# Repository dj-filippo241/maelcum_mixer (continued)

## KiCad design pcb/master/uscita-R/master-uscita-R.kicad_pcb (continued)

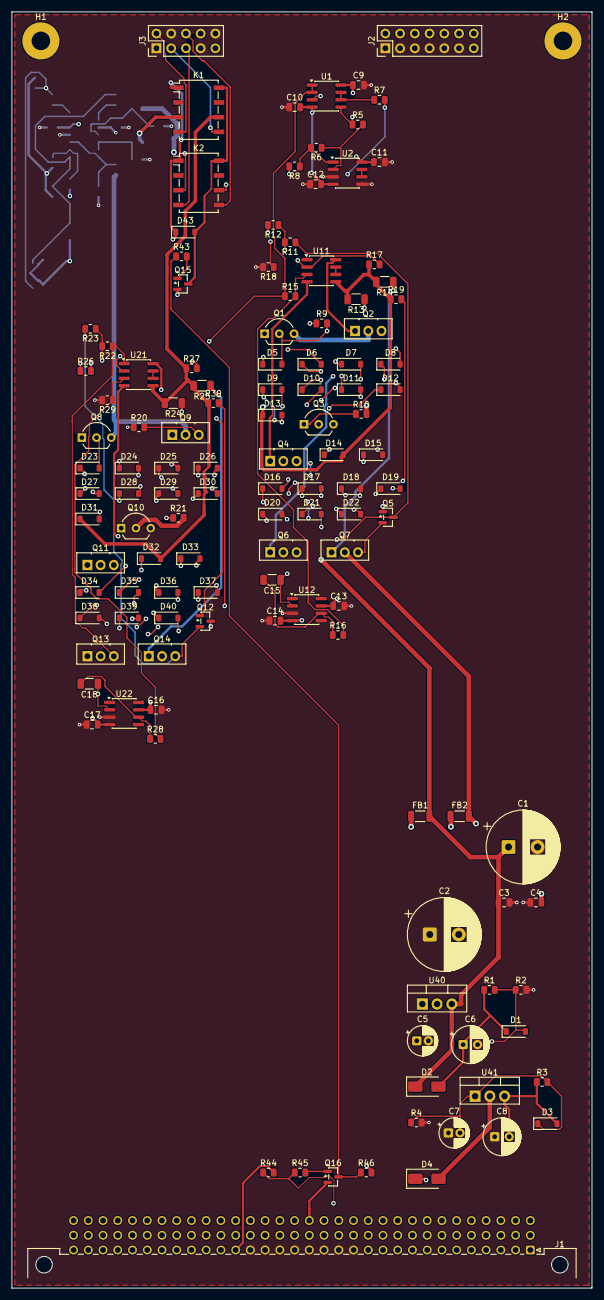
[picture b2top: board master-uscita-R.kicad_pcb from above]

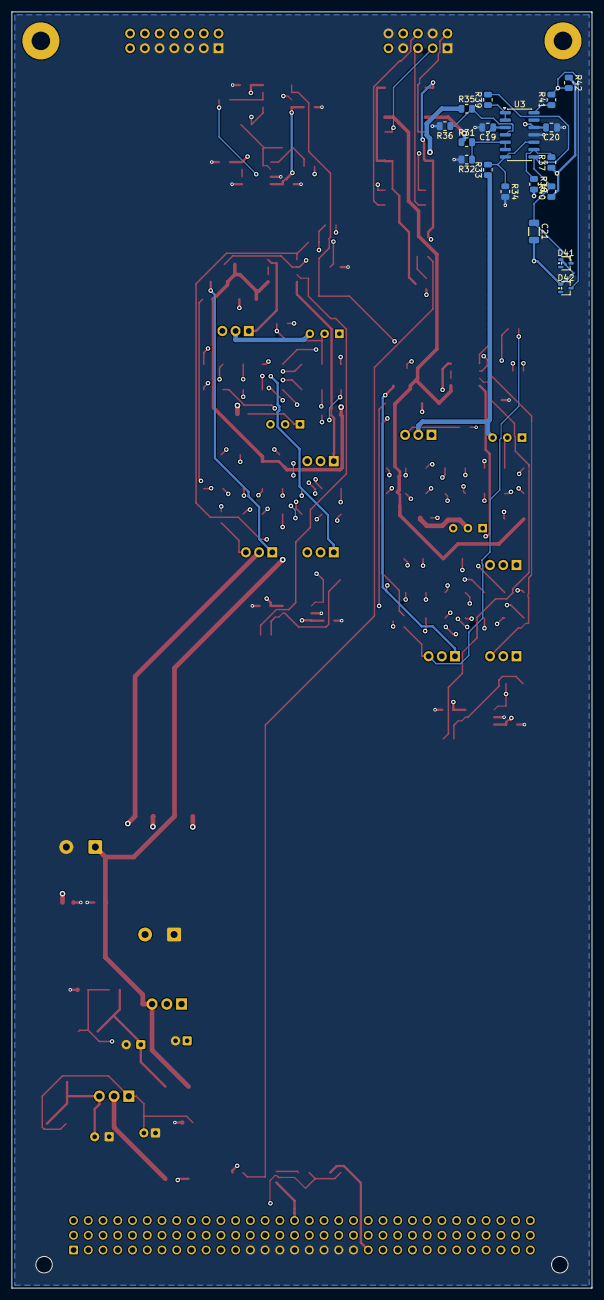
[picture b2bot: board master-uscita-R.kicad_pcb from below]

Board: 4 copper layers, 100.0 x 220.0 mm, 144 parts (18 on the bottom side), 104 nets.

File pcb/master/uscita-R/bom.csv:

quantita;valore;impronta;riferimenti;nota
1;1000u 35V;CP_Radial_D12.5mm_P5.00mm;C1;bulk locale [M] (master-out §3.8)
2;15n C0G;C_1206_3216Metric;C15 C18;fc 0,048 Hz (Test 12)
1;1000u 35V;CP_Radial_D12.5mm_P5.00mm;C2;
1;1u;C_1206_3216Metric;C21;
2;100n 50V;C_0805_2012Metric;C3 C4;
2;10u 35V;CP_Radial_D5.0mm_P2.00mm;C5 C7;
2;47u 35V;CP_Radial_D6.3mm_P2.50mm;C6 C8;
10;100n;C_0805_2012Metric;C9 C10 C11 C12 C13 C14 C16 C17 C19 C20;
1;1N4148W;D_SOD-123;D1;scarica Cadj
1;S1G;D_SMA;D2;protezione inversa
37;1N4148W;D_SOD-123;D3 D5 D6 D7 D8 D9 D10 D11 D12 D13 D14 D15 D16 D17 D18 D19 D20 D21 D22 D23 D24 D25 D26 D27 D28 D29 D30 D31 D32 D33 D34 D35 D36 D37 D38 D39 D40;
1;S1G;D_SMA;D4;
2;BAT54W;SOT-323_SC-70;D41 D42;
1;1N4148W;D_SOD-123;D43;scarica delle bobine: 1,0 ms (RISULTATI-mute-ctrl)
2;ferrite 600R 2A;L_1206_3216Metric;FB1 FB2;
1;C96 maschio;DIN41612_C_3x32_Male_Horizontal_THT;J1;DIN 41612 C 3x32; classe MASTER-OUT (dec. 143): RAW+-26, +5V, CTRL_GND, c9
1;2x7 cavo piatto;PinHeader_2x07_P2.54mm_Vertical;J2;cavo piatto dalla scheda di segnale (stessa piedinatura del suo J2)
1;2x5 cavo;PinHeader_2x05_P2.54mm_Vertical;J3;NOTA: verso la schedina XLR/TRS sul retro (dec. 141)
1;G6K-2F DC5;Relay_DPDT_Omron_G6K-2F;K1;MASTER R caldo e freddo
1;G6K-2F DC5;Relay_DPDT_Omron_G6K-2F;K2;BOOTH R caldo e freddo
2;BF245A;TO-92_Inline_Wide;Q1 Q8;CCS ~4 mA (NJF245 in sim; Idss da selezionare)
1;AO3400A;SOT-23;Q15;driver dei relè, logic level
1;2N7002;SOT-23;Q16;inverte c9: c9 alto (muto) -> relè diseccitati
2;MJE340;TO-126-3_Vertical;Q2 Q9;pass del rail +: 0,75 W a riposo, rame >= 4 cm2 (v0.3 punto 1); pinout da verificare
2;BF245A;TO-92_Inline_Wide;Q3 Q10;CCS ~4 mA
2;MJE350;TO-126-3_Vertical;Q4 Q11;pass del rail -: 0,75 W a riposo, rame >= 4 cm2; pinout da verificare
2;BC847B;SOT-23;Q5 Q12;moltiplicatore di Vbe (QMULT in sim): vicino a Q1/Q2 per l'inseguimento termico
2;MJE340;TO-126-3_Vertical;Q6 Q13;finale +; corto: 106 mA auto-limitati, 1,0 W medi
2;MJE350;TO-126-3_Vertical;Q7 Q14;finale -
2;120 1%;R_0805_2012Metric;R1 R3;
2;2k2 1%;R_0805_2012Metric;R11 R22;
2;1k 1%;R_0805_2012Metric;R12 R23;
4;33 1%;R_1206_3216Metric;R13 R14 R24 R25;
1;1k 0.1%;R_0805_2012Metric;R15;Rsrc: con Rinj 1M attenua 0,999, Rf/Rg guadagna 1,001
1;1M 1%;R_0805_2012Metric;R16;iniezione del servo
3;1k 0.1%;R_0805_2012Metric;R17 R27 R29;
1;1M 1%;R_0805_2012Metric;R18;
2;220k 1%;R_0805_2012Metric;R19 R30;
1;1k62 1%;R_0805_2012Metric;R2;18,1 V
1;1k 0.1%;R_0805_2012Metric;R26;freddo invertente: resistenze appaiate 0,1 % (CMRR ~60 dB)
1;1M 1%;R_0805_2012Metric;R28;NOTA: servo sul piedino + con partitore 1M/1k (cella dei servo)
1;100k 0.1%;R_0805_2012Metric;R31;
2;118k 1%;R_0805_2012Metric;R33 R35;
4;10k 1%;R_0805_2012Metric;R34 R36 R37 R38;
2;4k7;R_0805_2012Metric;R39 R41;
1;1k62 1%;R_0805_2012Metric;R4;
1;680k;R_0805_2012Metric;R40;tenuta: 680k x 1u, soglia a meta' = 0,47 s
1;10k;R_0805_2012Metric;R42;NOTA: CLIP alto = LED acceso (clip)
1;100;R_0805_2012Metric;R43;
1;100k;R_0805_2012Metric;R44;pull-up come negli altri moduli: master assente = muto
1;1k;R_0805_2012Metric;R45;
1;10k;R_0805_2012Metric;R46;
3;10k 0.1%;R_0805_2012Metric;R5 R6 R32;
1;47;R_0805_2012Metric;R7;NOTA: 47 ohm di uscita prima del relè
5;47;R_0805_2012Metric;R8 R9 R10 R20 R21;
1;OPA1612AIDR;SOIC-8_3.9x4.9mm_P1.27mm;U1;NOTA: ricevitore del cavo J2 (il caldo e il freddo caricano 500 ohm); caldo del booth
1;OPA1612AIDR;SOIC-8_3.9x4.9mm_P1.27mm;U11;composito H: rail a bootstrap (dec. 86); niente 100n rail-OUT (v0.3c)
2;TL071;SOIC-8_3.9x4.9mm_P1.27mm;U12 U22;servo DC su +-18 statici (FET, Iq bassa: non pesa sul bootstrap)
1;OPA1612AIDR;SOIC-8_3.9x4.9mm_P1.27mm;U2;freddo del booth; sezione B libera a massa
1;OPA1612AIDR;SOIC-8_3.9x4.9mm_P1.27mm;U21;composito C: rail a bootstrap (dec. 86); niente 100n rail-OUT (v0.3c)
1;LM339;SOIC-14_3.9x8.7mm_P1.27mm;U3;NOTA: clip detector (correzione 20 della review)
1;LM317;TO-220-3_Vertical;U40;NOTA: +-18 locali, ~30 mA
1;LM337;TO-220-3_Vertical;U41;

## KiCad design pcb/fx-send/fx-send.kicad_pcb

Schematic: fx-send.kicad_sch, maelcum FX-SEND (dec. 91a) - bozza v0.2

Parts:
C1, C2: 220u 35V; CP_Radial_D8.0mm_P3.50mm
C3: 47u 10V; CP_Radial_D5.0mm_P2.00mm
C4, C8: 10u 35V; CP_Radial_D5.0mm_P2.00mm
C5, C9: 47u 35V; CP_Radial_D6.3mm_P2.50mm
C6, C10: 470u 25V; CP_Radial_D8.0mm_P3.50mm
C7, C11: 100u 25V; CP_Radial_D6.3mm_P2.50mm
C12, C13: 1u 50V; C_1206_3216Metric
C14, C15: 1u 25V; C_1206_3216Metric
C16, C17, C22, C23, C24, C25, C30, C31, C32, C33, C34, C35, C36, C37, C38, C39, C40, C41: 100n; C_0805_2012Metric
C18, C19, C26, C27: 180n C0G; C_1206_3216Metric
C20, C21, C28, C29: 10n C0G; C_1206_3216Metric
D1, D3: 1N4148W; D_SOD-123
D2, D4: S1G; D_SMA
FB1, FB2, FB3, FB4, FB5: ferrite 600R; L_1206_3216Metric
H1, H2: CHASSIS; MountingHole_3.2mm_M3_Pad
J1: C96 maschio; DIN41612_C_3x32_Male_Horizontal_THT
J2: 2x12 cavo piatto; PinHeader_2x12_P2.54mm_Vertical
J3: 1x6 bottoni; PinHeader_1x06_P2.54mm_Vertical
Q1: BD139; TO-126-3_Vertical
Q2: BD140; TO-126-3_Vertical
Q3, Q4, Q5, Q6: 2N7002; SOT-23
R1, R4: 120 1%; R_0805_2012Metric
R2, R5: 1k74 1%; R_0805_2012Metric
R3, R6, R37, R40, R43, R46, R47: 1k; R_0805_2012Metric
R7, R8, R36, R39, R42, R45, R48: 100k; R_0805_2012Metric
R9, R10, R22, R23: 324 0.1%; R_0805_2012Metric
R11, R24: 5k23 0.1%; R_0805_2012Metric
R12, R25: 2k49 0.1%; R_0805_2012Metric
R13, R14, R18, R19, R20, R21, R26, R27, R31, R32, R33, R34: 10k 0.1%; R_0805_2012Metric
R15, R16, R17, R28, R29, R30: 49k9 0.1%; R_0805_2012Metric
R35, R38, R41, R44: 10k; R_0805_2012Metric
U1: OPA1612AIDR; SOIC-8_3.9x4.9mm_P1.27mm
U2, U3, U4, U5: OPA1654AIDR; SOIC-14_3.9x8.7mm_P1.27mm
U6, U7: ADG1434YRUZ; TSSOP-20_4.4x6.5mm_P0.65mm
U10: LM317; TO-220-3_Vertical
U11: LM337; TO-220-3_Vertical
U12: 78L15; SOT-89-3
U13: 79L15; SOT-89-3

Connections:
+5V: FB5.1, J1.a21, J1.a22
+5VF: C3.1, FB5.2, J3.1, R48.2
+15SW: C14.1, C34.1, C36.1, U6.16 (VDD), U7.16 (VDD), U12.1 (OUT)
+18V: C7.1, C16.1, C22.1, C24.1, C30.1, C32.1, Q1.1 (E), U1.8 (V+), U2.4 (V+), U3.4 (V+), U4.4 (V+), U5.4 (V+)
-15SW: C15.2, C35.2, C37.2, U6.5 (VSS), U7.5 (VSS), U13.3 (VO)
-18V: C11.2, C17.2, C23.2, C25.2, C31.2, C33.2, Q2.1 (E), U1.4 (V-), U2.11 (V-), U3.11 (V-), U4.11 (V-), U5.11 (V-)
ADJ+: C4.1, D1.2 (A), R1.2, R2.1, U10.1 (ADJ)
ADJ-: C8.2, D3.1 (K), R4.2, R5.1, U11.1 (ADJ)
AGND: C1.2, C2.1, C4.2, C5.2, C6.2, C7.2, C8.1, C9.1, C10.1, C11.1, C12.2, C13.1, C14.2, C15.1, C16.2, C17.1, C22.2, C23.1, C24.2, C25.1, C30.2, C31.1, C32.2, C33.1, C34.2, C35.1, C36.2, C37.1, J1.a13, J1.a14, J1.a15, J1.a16, J1.a17, J1.a18, J1.a19, J1.a20, J1.b3, J1.b6, J1.b9, J1.b12, J1.b15, J1.b18, J1.b21, J1.b24, J1.b27, J1.b30, J2.1, J2.5, J2.9, J2.13, J2.17, J2.20, J2.23, J2.24, R2.2, R5.2, R7.2, R8.2, R12.2, R25.2, U2.3 (+), U2.10 (+), U2.12 (+), U3.3 (+), U3.10 (+), U3.12 (+), U6.4 (S1B), U6.6 (GND), U6.7 (S2B), U6.14 (S3B), U6.17 (S4B), U7.4 (S1B), U7.6 (GND), U7.7 (S2B), U7.14 (S3B), U7.17 (S4B), U12.2 (GND), U13.1 (GND)
ASG1: C38.1, R35.2, R36.1, R37.1, U6.1 (IN1), U7.1 (IN1)
ASG2: C39.1, R38.2, R39.1, R40.1, U6.10 (IN2), U7.10 (IN2)
ASG3: C40.1, R41.2, R42.1, R43.1, U6.11 (IN3), U7.11 (IN3)
ASG4: C41.1, R44.2, R45.1, R46.1, U6.20 (IN4), U7.20 (IN4)
BASE+: C6.1, Q1.3 (B), R3.2
BASE-: C10.2, Q2.3 (B), R6.2
BTN1: J3.2, R35.1
BTN2: J3.3, R38.1
BTN3: J3.4, R41.1
BTN4: J3.5, R44.1
CHASSIS: H1.1, H2.1, J1.a25, J1.a26
CTRL_GND: C3.2, C38.2, C39.2, C40.2, C41.2, J1.a23, J1.a24, J1.c16, J1.c20, J1.c24, J1.c28, J3.6, Q3.2 (S), Q4.2 (S), Q5.2 (S), Q6.2 (S), R36.2, R39.2, R42.2, R45.2
GLOBAL_MUTE: J1.c9, R47.1
INJ1_L: R18.1, U4.1, U4.2 (-)
INJ1_R: R31.1, U5.1, U5.2 (-)
INJ2_L: R19.1, U4.6 (-), U4.7
INJ2_R: R32.1, U5.6 (-), U5.7
INJ3_L: R20.1, U4.8, U4.9 (-)
INJ3_R: R33.1, U5.8, U5.9 (-)
INJ4_L: R21.1, U4.13 (-), U4.14
INJ4_R: R34.1, U5.13 (-), U5.14
LVL_W_L: J2.19, U6.2 (S1A), U6.9 (S2A), U6.12 (S3A), U6.19 (S4A)
LVL_W_R: J2.22, U7.2 (S1A), U7.9 (S2A), U7.12 (S3A), U7.19 (S4A)
MD1: Q3.3 (D), R37.2
MD2: Q4.3 (D), R40.2
MD3: Q5.3 (D), R43.2
MD4: Q6.3 (D), R46.2
MUTE_G: Q3.1 (G), Q4.1 (G), Q5.1 (G), Q6.1 (G), R47.2, R48.1
NA_L: C18.1, J2.2, R9.2
NA_R: C26.1, J2.6, R22.2
NB_L: C18.2, C19.1, J2.3, U2.2 (-)
NB_R: C26.2, C27.1, J2.7, U3.2 (-)
NC_L: C19.2, J2.4, R10.1
NC_R: C27.2, J2.8, R23.1
NHA_L: C20.2, C21.1, R11.1
NHA_R: C28.2, C29.1, R24.1
NHB_L: C21.2, R12.1, U2.5 (+)
NHB_R: C29.2, R25.1, U3.5 (+)
NSH_L: R15.2, R16.2, R17.1, U2.13 (-)
NSH_R: R28.2, R29.2, R30.1, U3.13 (-)
NVH_L: R13.2, R14.1, U2.9 (-)
NVH_R: R26.2, R27.1, U3.9 (-)
RAW+22: FB3.1, J1.a5, J1.a6
RAW+27: FB1.1, J1.a1, J1.a2
RAW-22: FB4.1, J1.a7, J1.a8
RAW-27: FB2.1, J1.a3, J1.a4
S1_OUT_L: J1.b4, R18.2
S1_OUT_R: J1.b5, R31.2
S2_OUT_L: J1.b7, R19.2
S2_OUT_R: J1.b8, R32.2
S3_OUT_L: J1.b10, R20.2
S3_OUT_R: J1.b11, R33.2
S4_OUT_L: J1.b13, R21.2
S4_OUT_R: J1.b14, R34.2
SEND_IN_L: J1.b1, R7.1, U1.3 (+)
SEND_IN_R: J1.b2, R8.1, U1.5 (+)
SW1_L: U4.3 (+), U6.3 (D1)
SW1_R: U5.3 (+), U7.3 (D1)
SW2_L: U4.5 (+), U6.8 (D2)
SW2_R: U5.5 (+), U7.8 (D2)
SW3_L: U4.10 (+), U6.13 (D3)
SW3_R: U5.10 (+), U7.13 (D3)
SW4_L: U4.12 (+), U6.18 (D4)
SW4_R: U5.12 (+), U7.18 (D4)
V22F+: C12.1, FB3.2, U12.3 (IN)
V22F-: C13.2, FB4.2, U13.2 (VI)
V27F+: C1.1, D2.1 (K), FB1.2, U10.3 (VI)
V27F-: C2.2, D4.2 (A), FB2.2, U11.2 (VI)
VHI_L: J2.18, R17.2, U2.14
VHI_R: J2.21, R30.2, U3.14
VHN_L: J2.10, R14.2, U2.8
VHN_R: J2.14, R27.2, U3.8
VHP_L: J2.12, R11.2, R13.1, U2.6 (-), U2.7
VHP_R: J2.16, R24.2, R26.1, U3.6 (-), U3.7
VLO_L: C20.1, R10.2, R15.1, U2.1
VLO_R: C28.1, R23.2, R28.1, U3.1
VPRE_L: R9.1, U1.1, U1.2 (-)
VPRE_R: R22.1, U1.6 (-), U1.7
VREG+: C5.1, D1.1 (K), D2.2 (A), Q1.2 (C), R1.1, R3.1, U10.2 (VO)
VREG-: C9.2, D3.2 (A), D4.1 (K), Q2.2 (C), R4.1, R6.1, U11.3 (VO)
WPH_L: J2.11, R16.1
WPH_R: J2.15, R29.1

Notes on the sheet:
BACKPLANE C96 (classe FX-SEND)
ALIMENTAZIONE +-18 audio, +-15 switch, +5
BUFFER IN (OPA1612)
EQ2 lato L (LOW 120 Hz + HIGH 4,5 kHz, fx-eq2-pot10k.cir)
INIEZIONE lato L (OPA1654 + 10k verso i bus)
EQ2 lato R (LOW 120 Hz + HIGH 4,5 kHz, fx-eq2-pot10k.cir)
INIEZIONE lato R (OPA1654 + 10k verso i bus)
ASSIGN S1-S4 (ADG1434 pi SPDT, soft-switch 1 ms, mute globale)
CAVO SCHEDA COMANDI (J2) e BOTTONI ASSIGN (J3)

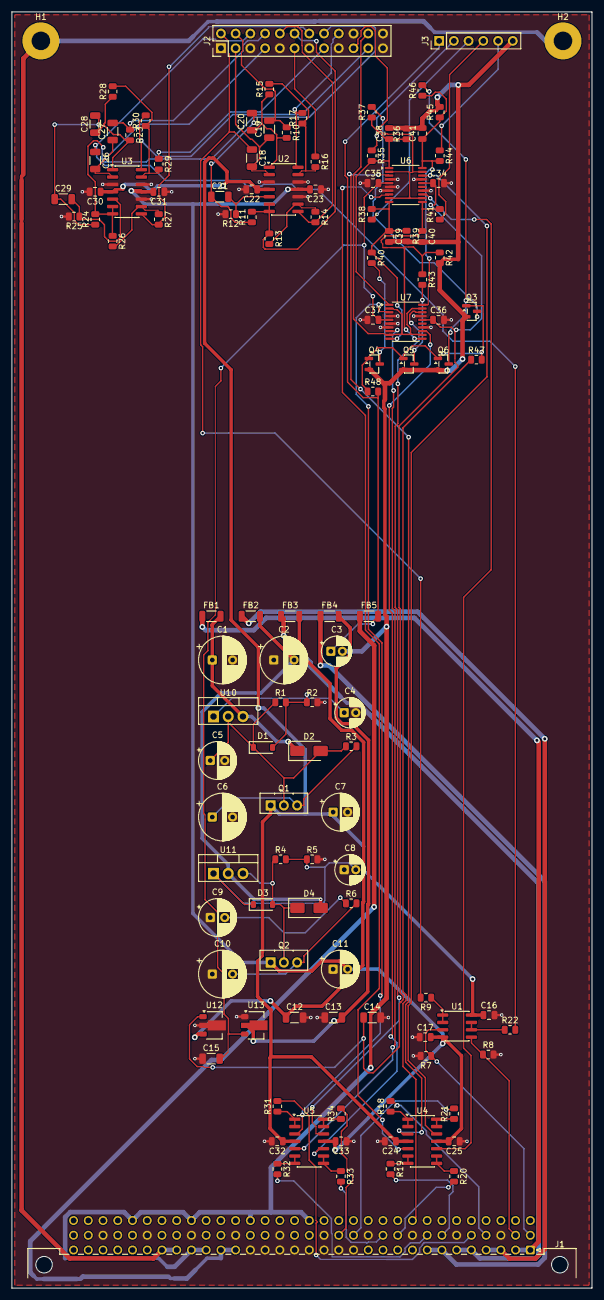
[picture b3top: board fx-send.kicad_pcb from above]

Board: 4 copper layers, 100.0 x 220.0 mm, 120 parts (0 on the bottom side), 91 nets.

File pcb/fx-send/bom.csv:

quantita;valore;impronta;riferimenti;nota
2;220u 35V;CP_Radial_D8.0mm_P3.50mm;C1 C2;
2;1u 50V;C_1206_3216Metric;C12 C13;
2;1u 25V;C_1206_3216Metric;C14 C15;
18;100n;C_0805_2012Metric;C16 C17 C22 C23 C24 C25 C30 C31 C32 C33 C34 C35 C36 C37 C38 C39 C40 C41;
4;180n C0G;C_1206_3216Metric;C18 C19 C26 C27;
4;10n C0G;C_1206_3216Metric;C20 C21 C28 C29;
1;47u 10V;CP_Radial_D5.0mm_P2.00mm;C3;
2;10u 35V;CP_Radial_D5.0mm_P2.00mm;C4 C8;
2;47u 35V;CP_Radial_D6.3mm_P2.50mm;C5 C9;
2;470u 25V;CP_Radial_D8.0mm_P3.50mm;C6 C10;
2;100u 25V;CP_Radial_D6.3mm_P2.50mm;C7 C11;
1;1N4148W;D_SOD-123;D1;scarica Cadj
1;S1G;D_SMA;D2;protezione inversa
1;1N4148W;D_SOD-123;D3;
1;S1G;D_SMA;D4;
5;ferrite 600R;L_1206_3216Metric;FB1 FB2 FB3 FB4 FB5;
1;C96 maschio;DIN41612_C_3x32_Male_Horizontal_THT;J1;DIN 41612 C 3x32, angolo retto
1;2x12 cavo piatto;PinHeader_2x12_P2.54mm_Vertical;J2;cavo piatto corto verso la scheda comandi (pot a bordo, dec. 133)
1;1x6 bottoni;PinHeader_1x06_P2.54mm_Vertical;J3;bottoni assign dal pannello del canale (logica +5 V, dec. 133)
1;BD139;TO-126-3_Vertical;Q1;
1;BD140;TO-126-3_Vertical;Q2;
4;2N7002;SOT-23;Q3 Q4 Q5 Q6;
2;120 1%;R_0805_2012Metric;R1 R4;
2;5k23 0.1%;R_0805_2012Metric;R11 R24;
2;2k49 0.1%;R_0805_2012Metric;R12 R25;sim 2,5k: E96 2,49k
12;10k 0.1%;R_0805_2012Metric;R13 R14 R18 R19 R20 R21 R26 R27 R31 R32 R33 R34;
6;49k9 0.1%;R_0805_2012Metric;R15 R16 R17 R28 R29 R30;
1;1k74 1%;R_0805_2012Metric;R2;E96 1,74k = 19,4 V (1,72k = 19,2 V non esiste all'1 %)
1;1k;R_0805_2012Metric;R3;NOTA: cap-moltiplicatore scalato a ~50 mA (sim: 47R/10mF per 0,85 A)
4;10k;R_0805_2012Metric;R35 R38 R41 R44;
4;1k;R_0805_2012Metric;R37 R40 R43 R46;NOTA: mute a 0,45 V (VIL 0,8 V), rampa ~0,09 ms
1;100k;R_0805_2012Metric;R48;c9 alto = muto (fail-safe), RISULTATI-mute-ctrl
1;1k74 1%;R_0805_2012Metric;R5;
2;1k;R_0805_2012Metric;R6 R47;
1;100k;R_0805_2012Metric;R7;NOTA: tiene l'ingresso a massa senza canale
5;100k;R_0805_2012Metric;R8 R36 R39 R42 R45;
4;324 0.1%;R_0805_2012Metric;R9 R10 R22 R23;
1;OPA1612AIDR;SOIC-8_3.9x4.9mm_P1.27mm;U1;
1;LM317;TO-220-3_Vertical;U10;
1;LM337;TO-220-3_Vertical;U11;
1;78L15;SOT-89-3;U12;
1;79L15;SOT-89-3;U13;
4;OPA1654AIDR;SOIC-14_3.9x8.7mm_P1.27mm;U2 U4 U3 U5;
2;ADG1434YRUZ;TSSOP-20_4.4x6.5mm_P0.65mm;U6 U7;pinout e tabella di verità verificati, Rev. E

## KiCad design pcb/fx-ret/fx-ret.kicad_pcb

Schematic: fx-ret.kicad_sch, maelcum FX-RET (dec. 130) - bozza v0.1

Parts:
C1, C2: 220u 35V; CP_Radial_D8.0mm_P3.50mm
C3: 47u 10V; CP_Radial_D5.0mm_P2.00mm
C4, C8: 10u 35V; CP_Radial_D5.0mm_P2.00mm
C5, C9: 47u 35V; CP_Radial_D6.3mm_P2.50mm
C6, C10: 470u 25V; CP_Radial_D8.0mm_P3.50mm
C7, C11: 100u 25V; CP_Radial_D6.3mm_P2.50mm
C12, C13, C15, C16: 4u7 25V; C_1206_3216Metric
C14, C17: 10u 25V; C_1206_3216Metric
C18: 1u; C_1206_3216Metric
C19, C20, C23, C24, C25, C26, C29, C30, C31, C32, C33, C34, C39, C40, C41, C42, C47, C48, C51, C52, C53, C54, C56, C57, C59, C60, C62, C63: 100n; C_0805_2012Metric
C21, C22: 10p C0G; C_0805_2012Metric
C27, C28: 15n C0G; C_1206_3216Metric
C35, C36, C43, C44: 180n C0G; C_1206_3216Metric
C37, C38, C45, C46: 10n C0G; C_1206_3216Metric
C49: 47p C0G; C_0805_2012Metric
C50: 100n C0G; C_1206_3216Metric
C55, C58: 22p C0G; C_0805_2012Metric
C61: 56n C0G; C_1210_3225Metric
D1, D3, D10, D11, D12, D13: 1N4148W; D_SOD-123
D2, D4: S1G; D_SMA
D5: LM4040-5.0; SOT-23
D6, D7, D8, D9: TVS bidir <=5 pF; D_SOD-323
FB1, FB2, FB3: ferrite 600R; L_1206_3216Metric
H1, H2: CHASSIS; MountingHole_3.2mm_M3_Pad
J1: C96 maschio; DIN41612_C_3x32_Male_Horizontal_THT
J2: 2x18 cavo piatto; PinHeader_2x18_P2.54mm_Vertical
J3: 1x7 jack pedale; PinHeader_1x07_P2.54mm_Vertical
J4: 2x16 ponte reroute; PinHeader_2x16_P2.54mm_Vertical
Q40: BD139; TO-126-3_Vertical
Q41: BD140; TO-126-3_Vertical
R1, R4: 120 1%; R_0805_2012Metric
R2, R5: 1k74 1%; R_0805_2012Metric
R3, R6, R53: 1k; R_0805_2012Metric
R7, R8: 150k 0.1%; R_0805_2012Metric
R9: 1k5; R_0805_2012Metric
R10, R11, R12, R14, R18, R23, R33, R34, R45, R46, R55, R56, R57, R58, R59, R60, R61, R62, R82: 10k 0.1%; R_0805_2012Metric
R13, R15, R16, R21: 100; R_0805_2012Metric
R17, R19, R20, R22, R24, R25: 1M; R_0805_2012Metric
R26, R38: 1k24 0.1%; R_0805_2012Metric
R27, R39: 3k24 0.1%; R_0805_2012Metric
R28, R40, R52: 4k02 0.1%; R_0805_2012Metric
R29, R30, R41, R42: 324 0.1%; R_0805_2012Metric
R31, R43: 5k23 0.1%; R_0805_2012Metric
R32, R44: 2k49 0.1%; R_0805_2012Metric
R35, R36, R37, R47, R48, R49: 49k9 0.1%; R_0805_2012Metric
R50, R51, R63, R67, R69, R73: 20k 0.1%; R_0805_2012Metric
R54: 3M; R_0805_2012Metric
R64, R70: 6k19; R_0805_2012Metric
R65, R71: 150k; R_0805_2012Metric
R66, R72: 51; R_0805_2012Metric
R68, R74: 47; R_0805_2012Metric
R75: 43.2k 0.1%; R_0805_2012Metric
R76: 68.1k 0.1%; R_0805_2012Metric
R77: 357k 0.1%; R_0805_2012Metric
R78: 20.0k 0.1%; R_0805_2012Metric
R79: 38.3k 0.1%; R_0805_2012Metric
R80: 976 0.1%; R_0805_2012Metric
R81: 1.33k 0.1%; R_0805_2012Metric
R83: 9k76 0.1%; R_0805_2012Metric
R84: 18k7 0.1%; R_0805_2012Metric
R85: 100k; R_0805_2012Metric
R86: 18k2 0.1%; R_0805_2012Metric
R87, R89: 1k 0.1%; R_0805_2012Metric
R88: 17k4 0.1%; R_0805_2012Metric
R90: 2M7; R_0805_2012Metric
RV1, RV2, RV4: 50k; Potentiometer_Bourns_3266W_Vertical
RV3: 2k; Potentiometer_Bourns_3266W_Vertical
U1, U2, U4, U5, U6, U30, U31, U46: OPA1612AIDR; SOIC-8_3.9x4.9mm_P1.27mm
U3: OPA1642AIDR; SOIC-8_3.9x4.9mm_P1.27mm
U7, U8, U9: OPA1654AIDR; SOIC-14_3.9x8.7mm_P1.27mm
U28, U29: V2181L; SOIC-8_3.9x4.9mm_P1.27mm
U40: LM317; TO-220-3_Vertical
U41: LM337; TO-220-3_Vertical
U44: LT3045EMSE; MSOP-12-1EP_3x4.039mm_P0.65mm_EP1.651x2.845mm
U45: LT3094EMSE; MSOP-12-1EP_3x4.039mm_P0.65mm_EP1.651x2.845mm

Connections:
+5V: FB3.1, J1.a21, J1.a22
+5VF: C3.1, FB3.2, J2.33
+15LN: C14.1, C19.1, C62.1, J4.7, R9.1, RV1.1, RV2.1, RV4.1, U31.8 (V+), U44.10 (OUTS), U44.11 (OUT), U44.12 (OUT), U46.8 (V+)
+18V: C7.1, C13.1, C23.1, C25.1, C29.1, C31.1, C33.1, C39.1, C41.1, C47.1, C51.1, C53.1, C56.1, C59.1, J4.1, J4.2, Q40.1 (E), U1.8 (V+), U2.8 (V+), U3.8 (V+), U4.8 (V+), U5.8 (V+), U6.8 (V+), U7.4 (V+), U8.4 (V+), U9.4 (V+), U28.7 (V+), U29.7 (V+), U30.8 (V+), U44.1 (IN), U44.2 (IN), U44.3 (IN), U44.4 (EN/UV), U44.7 (PGFB)
+REF5: J2.24, J4.11, R10.1, U46.1, U46.2 (-)
-15LN: C17.2, C20.2, C63.2, J4.8, RV1.3, RV2.3, RV4.3, U31.4 (V-), U45.10 (OUTS), U45.11 (OUT), U45.12 (OUT), U46.4 (V-)
-18V: C11.2, C16.2, C24.2, C26.2, C30.2, C32.2, C34.2, C40.2, C42.2, C48.2, C52.2, C54.2, C57.2, C60.2, J4.5, J4.6, Q41.1 (E), R64.2, R70.2, U1.4 (V-), U2.4 (V-), U3.4 (V-), U4.4 (V-), U5.4 (V-), U6.4 (V-), U7.11 (V-), U8.11 (V-), U9.11 (V-), U30.4 (V-), U45.1 (IN), U45.2 (IN), U45.3 (EN/UV), U45.5 (PGFB), U45.13 (IN)
-REF5: J4.12, R11.2, R77.2, R79.2, R81.2, U46.7
ADJ+: C4.1, D1.2 (A), R1.2, R2.1, U40.1 (ADJ)
ADJ-: C8.2, D3.1 (K), R4.2, R5.1, U41.1 (ADJ)
AGND: C1.2, C2.1, C4.2, C5.2, C6.2, C7.2, C8.1, C9.1, C10.1, C11.1, C12.2, C13.2, C14.2, C15.1, C16.1, C17.1, C18.2, C19.2, C20.1, C23.2, C24.1, C25.2, C26.1, C29.2, C30.1, C31.2, C32.1, C33.2, C34.1, C39.2, C40.1, C41.2, C42.1, C47.2, C48.1, C50.2, C51.2, C52.1, C53.2, C54.1, C56.2, C57.1, C59.2, C60.1, C62.2, C63.1, D5.2 (A), D6.2 (A2), D7.2 (A2), D8.2 (A2), D9.2 (A2), J1.a13, J1.a14, J1.a15, J1.a16, J1.a17, J1.a18, J1.a19, J1.a20, J1.b3, J1.b6, J1.b9, J1.b12, J1.b15, J1.b18, J1.b21, J1.b24, J1.b27, J1.b30, J2.1, J2.5, J2.9, J2.16, J2.23, J2.30, J2.32, J2.35, J2.36, J3.3, J3.6, J4.3, J4.4, J4.9, J4.10, J4.13, J4.14, J4.17, J4.18, J4.27, J4.28, R2.2, R5.2, R7.2, R8.2, R17.2, R22.2, R32.2, R44.2, R52.2, R54.2, R66.2, R72.2, R85.2, R87.2, R89.2, U1.3 (+), U1.5 (+), U4.3 (+), U4.5 (+), U5.3 (+), U5.5 (+), U6.3 (+), U6.5 (+), U7.3 (+), U7.10 (+), U7.12 (+), U8.3 (+), U8.10 (+), U8.12 (+), U9.12 (+), U28.2 (EC+), U28.6 (GND), U29.2 (EC+), U29.6 (GND), U30.3 (+), U30.5 (+), U31.3 (+), U31.5 (+), U44.6 (ILIM), U44.9 (GND), U44.13 (GND), U45.6 (ILIM), U45.9 (GND), U46.5 (+)
BASE+: C6.1, Q40.3 (B), R3.2
BASE-: C10.2, Q41.3 (B), R6.2
BOUT_L: R18.1, R26.1, U3.1
BOUT_R: R23.1, R38.1, U3.7
BSUM_L: C21.2, R12.2, U1.1, U2.3 (+)
BSUM_R: C22.2, R14.2, U1.7, U2.5 (+)
BUS_IN_L: C21.1, J1.b1, R12.1, U1.2 (-)
BUS_IN_R: C22.1, J1.b2, R14.1, U1.6 (-)
CHASSIS: H1.1, H2.1, J1.a25, J1.a26, J3.7
CTRL_GND: C3.2, J1.a23, J1.a24, J1.c16, J1.c20, J1.c24, J1.c28, J2.34
CVP_F: C61.2, R84.2, R86.1, R88.1, U31.7
D1A: D10.2 (A), R53.2
DIR1_L: J4.19, R55.1
DIR1_R: J4.20, R56.1
DIR2_L: J4.21, R57.1
DIR2_R: J4.22, R58.1
DIR3_L: J4.23, R59.1
DIR3_R: J4.24, R60.1
DIR4_L: J4.25, R61.1
DIR4_R: J4.26, R62.1
DOUT: C49.1, R53.1, U9.7
ECF_L: R86.2, R87.1, U28.3 (EC-)
ECF_R: R89.1, R90.2, RV3.2, RV3.3, U29.3 (EC-)
FAD_L: C55.2, R67.2, R68.1, U30.1
FAD_R: C58.2, R73.2, R74.1, U30.7
G2_L: R28.2, R29.1, U5.7
G2_R: R40.2, R41.1, U6.7
GA_L: J2.2, R26.2
GA_R: J2.6, R38.2
GW_L: J2.3, U5.2 (-)
GW_R: J2.7, U6.2 (-)
HOLD: C49.2, C50.1, D10.1 (K), R54.1, U9.6 (-), U9.10 (+)
JRET_L: J3.4, R16.1
JRET_R: J3.5, R21.1
LT_F: R88.2, RV3.1
MET: J2.31, U9.8, U9.9 (-)
MG: R50.2, R51.2, R52.1, U9.3 (+)
MGB: U9.1, U9.2 (-), U9.5 (+)
NA_L: C35.1, J2.10, R29.2
NA_R: C43.1, J2.17, R41.2
NB_L: C35.2, C36.1, J2.11, U7.2 (-)
NB_R: C43.2, C44.1, J2.18, U8.2 (-)
NC_L: C36.2, J2.12, R30.1
NC_R: C44.2, J2.19, R42.1
NFB_L: R18.2, R19.2, U3.2 (-)
NFB_R: R23.2, R24.2, U3.6 (-)
NHA_L: C37.2, C38.1, R31.1
NHA_R: C45.2, C46.1, R43.1
NHB_L: C38.2, R32.1, U7.5 (+)
NHB_R: C46.2, R44.1, U8.5 (+)
NIF_L: C55.1, R67.1, U28.8 (OUT), U30.2 (-)
NIF_R: C58.1, R73.1, U29.8 (OUT), U30.6 (-)
NP_F: C61.1, R83.2, R84.1, U31.6 (-)
NREF5I: R10.2, R11.1, U46.6 (-)
NSH_L: R35.2, R36.2, R37.1, U7.13 (-)
NSH_R: R47.2, R48.2, R49.1, U8.13 (-)
NU9: U9.13 (-), U9.14
NVH_L: R33.2, R34.1, U7.9 (-)
NVH_R: R45.2, R46.1, U8.9 (-)
O2A_L: J2.4, R20.1, R27.1, U5.1
O2A_R: J2.8, R25.1, R39.1, U6.1
OF_F: R90.1, RV4.2
PDRV_L: R13.1, U2.1, U2.2 (-)
PDRV_R: R15.1, U2.6 (-), U2.7
POT_F: J2.29, R75.1, R76.1, R78.1, R80.1, R85.1
POT_R1: J2.25, J4.29
POT_R2: J2.26, J4.30
POT_R3: J2.27, J4.31
POT_R4: J2.28, J4.32
RAW+22: J1.a5, J1.a6
RAW+27: FB1.1, J1.a1, J1.a2
RAW-22: J1.a7, J1.a8
RAW-27: FB2.1, J1.a3, J1.a4
REF5K: C18.1, D5.1 (K), R9.2, U46.3 (+)
RET_OUT_L: J1.b16, R68.2
RET_OUT_R: J1.b17, R74.2
RIN_L: D8.1 (A1), R16.2, R17.1, U3.3 (+)
RIN_R: D9.1 (A1), R21.2, R22.1, U3.5 (+)
RRN_L: J4.15, R37.2, R50.1, R63.1, U7.14
RRN_R: J4.16, R49.2, R51.1, R69.1, U8.14
S1_OUT_L: J1.b4, R55.2
S1_OUT_R: J1.b5, R56.2
S2_OUT_L: J1.b7, R57.2
S2_OUT_R: J1.b8, R58.2
S3_OUT_L: J1.b10, R59.2
S3_OUT_R: J1.b11, R60.2
S4_OUT_L: J1.b13, R61.2
S4_OUT_R: J1.b14, R62.2
SEND_L: D6.1 (A1), J3.1, R13.2
SEND_R: D7.1 (A1), J3.2, R15.2
SETN: C15.2, R8.1, U45.8 (SET)
SETP: C12.1, R7.1, U44.8 (SET)
SH_F: R82.2, R83.1, U31.1
SINT_L: C27.1, R20.2, U4.2 (-)
SINT_R: C28.1, R25.2, U4.6 (-)
SJ_F: D11.1 (K), D12.1 (K), D13.1 (K), R75.2, R82.1, U31.2 (-)
SN1_F: D11.2 (A), R76.2, R77.1
SN2_F: D12.2 (A), R78.2, R79.1
SN3_F: D13.2 (A), R80.2, R81.1
SW_fl: R65.1, RV1.2
SW_fr: R71.1, RV2.2
SYM_fl: R65.2, R66.1, U28.4 (SYM)
SYM_fr: R71.2, R72.1, U29.4 (SYM)
V27F+: C1.1, D2.1 (K), FB1.2, U40.3 (VI)
V27F-: C2.2, D4.2 (A), FB2.2, U41.2 (VI)
VEE_fl: R64.1, U28.5 (V-)
VEE_fr: R70.1, U29.5 (V-)
VHN_L: J2.13, R34.2, U7.8
VHN_R: J2.20, R46.2, U8.8
VHP_L: J2.15, R31.2, R33.1, U7.6 (-), U7.7
VHP_R: J2.22, R43.2, R45.1, U8.6 (-), U8.7
VINT_L: C27.2, R19.1, U4.1
VINT_R: C28.2, R24.1, U4.7
VIN_fl: R63.2, U28.1 (IN)
VIN_fr: R69.2, U29.1 (IN)
VK2_L: R27.2, R28.1, U5.6 (-)
VK2_R: R39.2, R40.1, U6.6 (-)
VLO_L: C37.1, R30.2, R35.1, U7.1
VLO_R: C45.1, R42.2, R47.1, U8.1
VREG+: C5.1, D1.1 (K), D2.2 (A), Q40.2 (C), R1.1, R3.1, U40.2 (VO)
VREG-: C9.2, D3.2 (A), D4.1 (K), Q41.2 (C), R4.1, R6.1, U41.3 (VO)
WPH_L: J2.14, R36.1
WPH_R: J2.21, R48.1

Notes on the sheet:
BACKPLANE C96 (classe FX-RET, dec. 130)
ALIMENTAZIONE +-18 audio, +5, +-15 LN, +-5 riferimento
SOMMA DEL BUS (slot 1, Rf 10k, Cf 10p) e DRIVER DEL PEDALE
RITORNO: protezione, buffer JFET g=1, servo DC (ritorno-buffer-g1.cir)
GAIN T2 (pot doppio 10k lin sul cavo, dec. 162; x1,24 todo 220) e EQ2
METER del ritorno (mono centrato, g = 0,288; detector meter-det-03s.cir)
PONTE verso la scheda REROUTE (J4) e 10k verso i bus S1-S4
FADER (2 VCA, shaper del fader, dec. 126) e USCITA verso MSUM (slot 6)
CAVO SCHEDA COMANDI (J2) e JACK DEL PEDALE (J3)

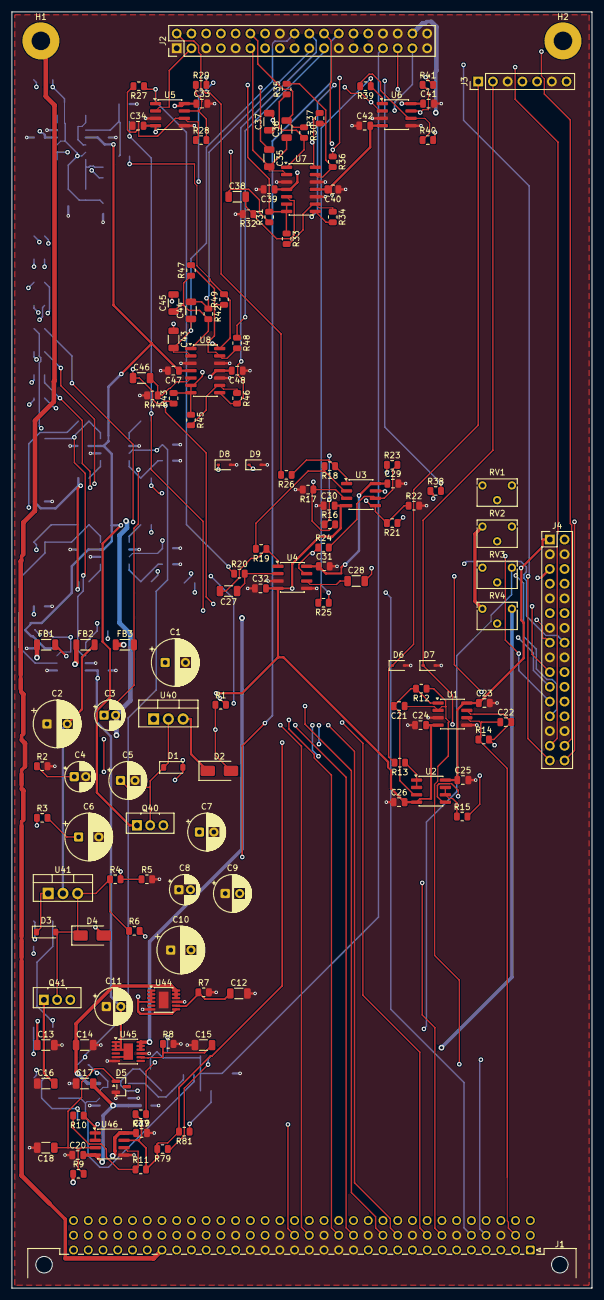
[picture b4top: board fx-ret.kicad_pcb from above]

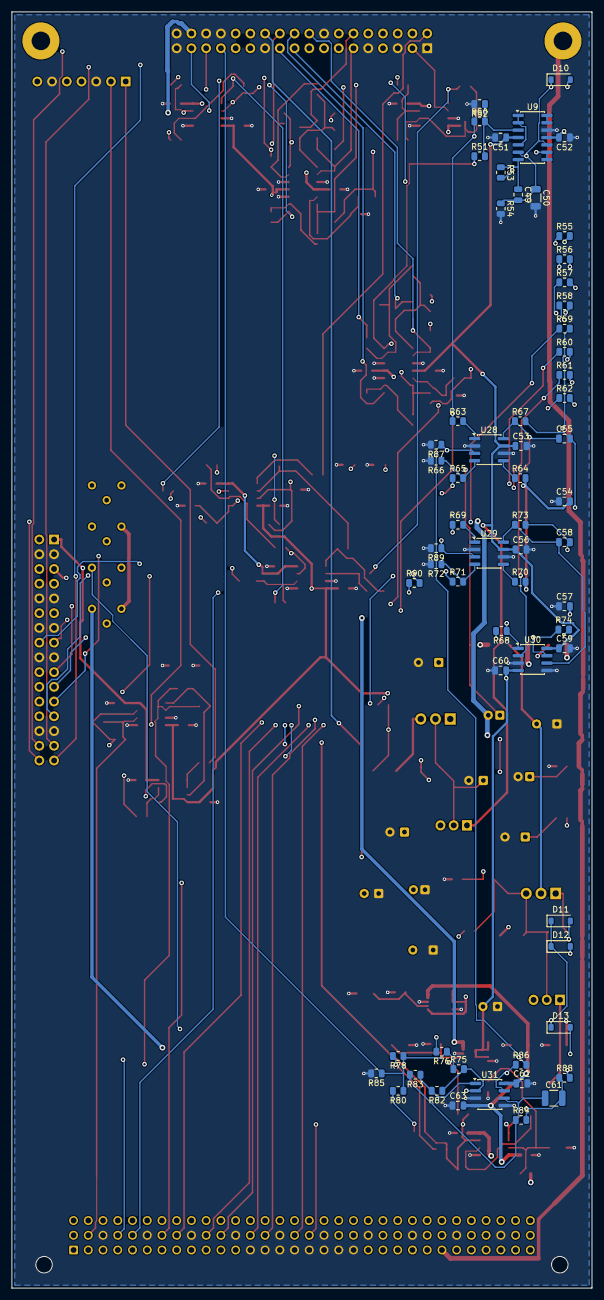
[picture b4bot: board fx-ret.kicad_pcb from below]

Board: 4 copper layers, 100.0 x 220.0 mm, 199 parts (62 on the bottom side), 134 nets.

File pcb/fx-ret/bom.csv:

quantita;valore;impronta;riferimenti;nota
2;220u 35V;CP_Radial_D8.0mm_P3.50mm;C1 C2;
1;4u7 25V;C_1206_3216Metric;C12;rumore del riferimento (datasheet: 4,7 uF)
3;4u7 25V;C_1206_3216Metric;C13 C15 C16;
2;10u 25V;C_1206_3216Metric;C14 C17;
1;1u;C_1206_3216Metric;C18;
28;100n;C_0805_2012Metric;C19 C20 C23 C24 C25 C26 C29 C30 C31 C32 C33 C34 C39 C40 C41 C42 C47 C48 C51 C52 C53 C54 C56 C57 C59 C60 C62 C63;
2;10p C0G;C_0805_2012Metric;C21 C22;Cf obbligatorio sul net lungo (fx-module §2bis.4)
2;15n C0G;C_1206_3216Metric;C27 C28;integratore 1M/15n
1;47u 10V;CP_Radial_D5.0mm_P2.00mm;C3;
4;180n C0G;C_1206_3216Metric;C35 C36 C43 C44;
4;10n C0G;C_1206_3216Metric;C37 C38 C45 C46;
2;10u 35V;CP_Radial_D5.0mm_P2.00mm;C4 C8;
1;47p C0G;C_0805_2012Metric;C49;
2;47u 35V;CP_Radial_D6.3mm_P2.50mm;C5 C9;
1;100n C0G;C_1206_3216Metric;C50;hold: niente altro sul nodo (sim/meter)
2;22p C0G;C_0805_2012Metric;C55 C58;
2;470u 25V;CP_Radial_D8.0mm_P3.50mm;C6 C10;
1;56n C0G;C_1210_3225Metric;C61;NOTA: smoothing 1 ms (dec. 80) come C sulla Rf: 18,7k x 56n = 1,05 ms
2;100u 25V;CP_Radial_D6.3mm_P2.50mm;C7 C11;
1;1N4148W;D_SOD-123;D1;scarica Cadj
1;S1G;D_SMA;D2;protezione inversa
5;1N4148W;D_SOD-123;D3 D10 D11 D12 D13;
1;S1G;D_SMA;D4;
1;LM4040-5.0;SOT-23;D5;
2;TVS bidir <=5 pF;D_SOD-323;D6 D7;NOTA: parte da scegliere (TVS bidirezionale low-cap, fx-module §8.4)
2;TVS bidir <=5 pF;D_SOD-323;D8 D9;NOTA: parte da scegliere (<= 5 pF)
3;ferrite 600R;L_1206_3216Metric;FB1 FB2 FB3;
1;C96 maschio;DIN41612_C_3x32_Male_Horizontal_THT;J1;DIN 41612 C 3x32, angolo retto
1;2x18 cavo piatto;PinHeader_2x18_P2.54mm_Vertical;J2;cavo piatto corto verso la scheda comandi dietro il pannello (dec. 133)
1;1x7 jack pedale;PinHeader_1x07_P2.54mm_Vertical;J3;NOTA: cavo verso i jack SEND/RETURN del pedale; posizione dei jack non decisa
1;2x16 ponte reroute;PinHeader_2x16_P2.54mm_Vertical;J4;NOTA: cavo piatto 2x16 verso la scheda reroute (divisione PROVVISORIA, NOTE.md)
1;BD139;TO-126-3_Vertical;Q40;
1;BD140;TO-126-3_Vertical;Q41;
2;120 1%;R_0805_2012Metric;R1 R4;
9;10k 0.1%;R_0805_2012Metric;R10 R11 R12 R14 R33 R34 R45 R46 R82;
2;100;R_0805_2012Metric;R13 R15;R serie verso il jack (fx-module §4)
2;100;R_0805_2012Metric;R16 R21;Rprot
2;1M;R_0805_2012Metric;R17 R22;Rbias 1 Mohm (fx-module §4)
2;10k 0.1%;R_0805_2012Metric;R18 R23;Rf2: inseguitore, servo sul nodo FB
2;1M;R_0805_2012Metric;R19 R24;Rinj
1;1k74 1%;R_0805_2012Metric;R2;E96 1,74k = 19,4 V (fx-send NOTE punto 16)
2;1M;R_0805_2012Metric;R20 R25;Rsi: il servo legge il primo invertente (fx-module §5)
2;1k24 0.1%;R_0805_2012Metric;R26 R38;Ra
2;3k24 0.1%;R_0805_2012Metric;R27 R39;
2;4k02 0.1%;R_0805_2012Metric;R28 R40;x1,24 (todo 220)
4;324 0.1%;R_0805_2012Metric;R29 R30 R41 R42;
1;1k;R_0805_2012Metric;R3;NOTA: cap-moltiplicatore come il FX-SEND (~50 mA): da riscalare sulla corrente vera
2;5k23 0.1%;R_0805_2012Metric;R31 R43;
2;2k49 0.1%;R_0805_2012Metric;R32 R44;sim 2,5k: E96 2,49k
6;49k9 0.1%;R_0805_2012Metric;R35 R36 R37 R47 R48 R49;
1;1k74 1%;R_0805_2012Metric;R5;
1;20k 0.1%;R_0805_2012Metric;R50;NOTA: (L+R)/2 con due 20k: 10k equivalenti
5;20k 0.1%;R_0805_2012Metric;R51 R63 R67 R69 R73;
1;4k02 0.1%;R_0805_2012Metric;R52;g = 4,02/14,02 = 0,287 (doc 0,288), come il master
1;3M;R_0805_2012Metric;R54;release 0,3 s (dec. 81)
8;10k 0.1%;R_0805_2012Metric;R55 R56 R57 R58 R59 R60 R61 R62;R lato sorgente sul net del bus (driver d'iniezione sulla scheda reroute)
2;1k;R_0805_2012Metric;R6 R53;
2;6k19;R_0805_2012Metric;R64 R70;5,1k del datasheet a -15 V riscalato a -18 V (come il master)
2;150k;R_0805_2012Metric;R65 R71;
2;51;R_0805_2012Metric;R66 R72;
2;47;R_0805_2012Metric;R68 R74;NOTA: l'I/V fa da buffer d'uscita (<= 50 ohm), 47R verso il backplane
2;150k 0.1%;R_0805_2012Metric;R7 R8;
1;43.2k 0.1%;R_0805_2012Metric;R75;
1;68.1k 0.1%;R_0805_2012Metric;R76;
1;357k 0.1%;R_0805_2012Metric;R77;
1;20.0k 0.1%;R_0805_2012Metric;R78;
1;38.3k 0.1%;R_0805_2012Metric;R79;
1;976 0.1%;R_0805_2012Metric;R80;
1;1.33k 0.1%;R_0805_2012Metric;R81;
1;9k76 0.1%;R_0805_2012Metric;R83;
1;18k7 0.1%;R_0805_2012Metric;R84;stadio del partitore x(-1,916): CV al pin = out/10,02 (todo 281)
1;100k;R_0805_2012Metric;R85;pot staccato = shaper a 0 V (come il master)
1;18k2 0.1%;R_0805_2012Metric;R86;
2;1k 0.1%;R_0805_2012Metric;R87 R89;
1;17k4 0.1%;R_0805_2012Metric;R88;
1;1k5;R_0805_2012Metric;R9;NOTA: ~6,7 mA nel riferimento (come il master)
1;2M7;R_0805_2012Metric;R90;partitore da ~950 ohm: 2,7M = +-5,3 mV come prima
2;50k;Potentiometer_Bourns_3266W_Vertical;RV1 RV2;trim di simmetria (THD minima)
1;2k;Potentiometer_Bourns_3266W_Vertical;RV3;trim di law, 25 giri (vca-trim §3.2): montato solo se la coppia esce da 0,5 dB
1;50k;Potentiometer_Bourns_3266W_Vertical;RV4;trim d'offset di coppia
1;OPA1612AIDR;SOIC-8_3.9x4.9mm_P1.27mm;U1;somma del bus, invertente
1;OPA1612AIDR;SOIC-8_3.9x4.9mm_P1.27mm;U2;driver del pedale, inseguitore (pad fisso 0 dB, dec. 108)
2;V2181L;SOIC-8_3.9x4.9mm_P1.27mm;U28 U29;
1;OPA1642AIDR;SOIC-8_3.9x4.9mm_P1.27mm;U3;buffer JFET hi-Z (OPA1642, SBOS484D)
1;OPA1612AIDR;SOIC-8_3.9x4.9mm_P1.27mm;U30;I/V del fader
1;OPA1612AIDR;SOIC-8_3.9x4.9mm_P1.27mm;U31;shaper F
1;OPA1612AIDR;SOIC-8_3.9x4.9mm_P1.27mm;U4;servo DC L e R
1;LM317;TO-220-3_Vertical;U40;
1;LM337;TO-220-3_Vertical;U41;
1;LT3045EMSE;MSOP-12-1EP_3x4.039mm_P0.65mm_EP1.651x2.845mm;U44;EN/UV a IN; ILIM a massa; PG libero; PGFB a IN (come master-segnale.py)
1;LT3094EMSE;MSOP-12-1EP_3x4.039mm_P0.65mm_EP1.651x2.845mm;U45;EN/UV a IN; PG libero; PGFB a IN; ILIM a massa; VIOC libero
1;OPA1612AIDR;SOIC-8_3.9x4.9mm_P1.27mm;U46;+5 e -5 V di riferimento
2;OPA1612AIDR;SOIC-8_3.9x4.9mm_P1.27mm;U5 U6;GAIN T2: cursore a massa virtuale, poi invertente x1,24
2;OPA1654AIDR;SOIC-14_3.9x8.7mm_P1.27mm;U7 U8;EQ2: LOW, HIGH follower, HIGH invertente, HIGH somma
1;OPA1654AIDR;SOIC-14_3.9x8.7mm_P1.27mm;U9;inseguitore di scala, superdiodo, buffer dell'hold; quarta sezione libera
